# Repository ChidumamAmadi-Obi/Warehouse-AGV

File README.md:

# Warehouse AGV 
*(3rd Year Capstone Project)*

Automated Guided Vehicle that transports loads along predetermined paths. Features line following, obstacle detection, location tracking, and PS4 controller input via Bluetooth. Built with a Finite State Machine (FSM) architecture with LED/buzzer alerts for user feedback.

### Links
 - [**Demo Video**](https://github.com/user-attachments/assets/4ddb8e79-1c91-4d6d-a385-816ef9b9aa53) <br>
 - [*STL Files*](https://github.com/ChidumamAmadi-Obi/Warehouse-AGV/tree/main/mechanical%20design/STL%20FIles) <br>
 - [*Gerber Files*](https://github.com/ChidumamAmadi-Obi/Warehouse-AGV/tree/main/hardware/gerbers-files) <br>
 - [*Schematic Diagram*](https://github.com/ChidumamAmadi-Obi/Warehouse-AGV/blob/main/hardware/schematic-pdf.pdf) <br>
 - [*Firmware Source Code*](https://github.com/ChidumamAmadi-Obi/Warehouse-AGV/tree/main/firmware) <br>

### Features
- PS4 Bluetooth controller for destination waypoints
- Line following with obstacle avoidance
- Real-time location tracking with waypoint markers on track
- Finite State Machine with robust transitions 
- Visual/audio alerts (LEDs & buzzer)
- 3D printable chassis (STL files included)
- Custom PCB with integrated motor driver, voltage regulation and sensor headers

### Firmware Prerequisites
The chosen controller needs to be paired with the ESP32’s Bluetooth MAC address before use.
Additionally, project also relies on [this](https://github.com/pablomarquez76/PS4_Controller_Host/tree/main) ps4 controller library to handle the Bluetooth communication between the ESP32 and the PS4 controller.

Once this library is installed it is to be inserted into the `./lib` PlatformIO project directory

### Custom PCB

### Schematic Diagram

### State Diagram

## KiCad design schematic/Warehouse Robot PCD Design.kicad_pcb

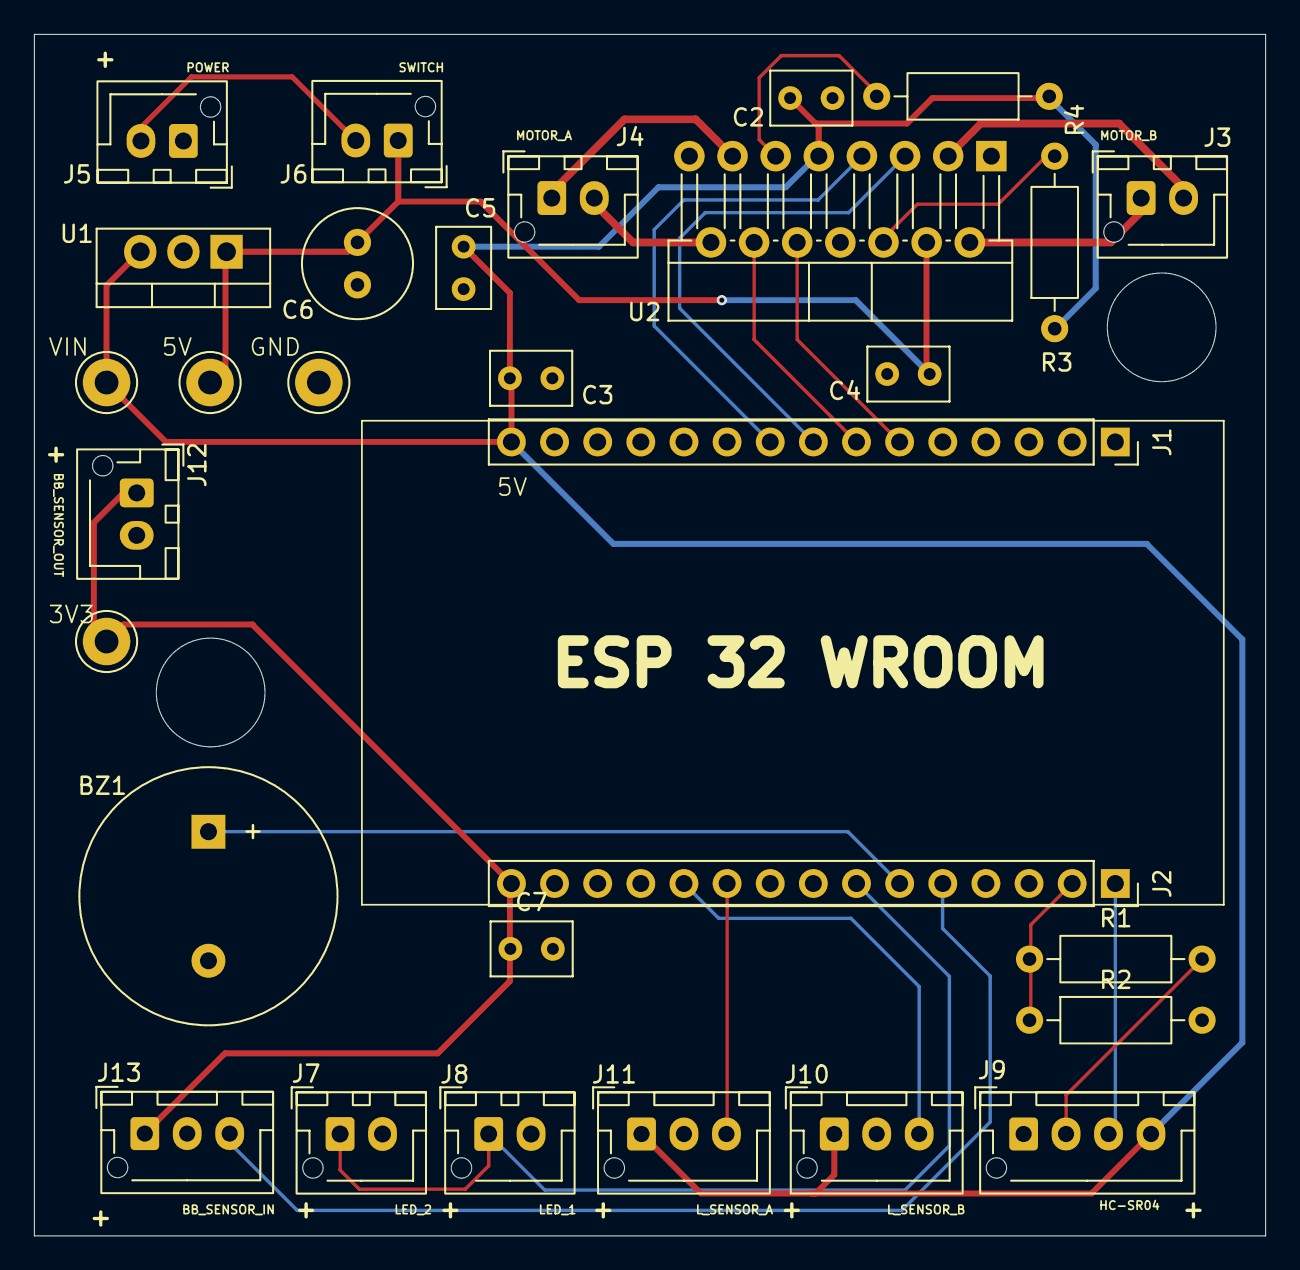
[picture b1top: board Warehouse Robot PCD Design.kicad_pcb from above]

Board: 2 copper layers, 72.5 x 70.8 mm, 30 parts (0 on the bottom side), 23 nets.

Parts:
BZ1: Buzzer; Buzzer_15x7.5RM7.6
C2, C5, C7: 1uf; C_Rect_L4.6mm_W3.0mm_P2.50mm_MKS02_FKP02
C3: 0.1uf; C_Rect_L4.6mm_W3.0mm_P2.50mm_MKS02_FKP02
C4: 10uf; C_Rect_L4.6mm_W3.0mm_P2.50mm_MKS02_FKP02
C6: 10uf; C_Radial_D6.3mm_H5.0mm_P2.50mm
J1, J2: Conn_01x15_Pin; PinSocket_1x15_P2.54mm_Vertical
J3, J4, J5, J6, J7, J8, J12: Conn_01x02; JST_XH_B2B-XH-AM_1x02_P2.50mm_Vertical
J9: Conn_01x04_Pin; JST_XH_B4B-XH-AM_1x04_P2.50mm_Vertical
J10, J11, J13: Conn_01x03_Pin; JST_XH_B3B-XH-AM_1x03_P2.50mm_Vertical
R1, R3, R4: 1k; R_Axial_DIN0207_L6.3mm_D2.5mm_P10.16mm_Horizontal
R2: 2k; R_Axial_DIN0207_L6.3mm_D2.5mm_P10.16mm_Horizontal
TP1, TP2, TP3, TP4: TestPoint; TestPoint_Loop_D3.50mm_Drill1.4mm_Beaded
U1: LM7805_TO220; TO-220-3_Vertical
U2: L298N; TO-220F-15_P2.54x5.08mm_StaggerOdd_Lead5.08mm_Vertical

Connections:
3v3: C7.1, J2.15, J12.1, J13.1, TP1.1
5v: C2.2, C3.1, C5.1, J1.15, J9.4, J10.1, J11.1, R3.1, R4.1, TP2.1, U1.3 (VO), U2.9 (Vss)
BB_OUT: J2.5, J13.3
ECHO: J2.2, R1.2, R2.1
GND: BZ1.2 (-), C2.1, C3.2, C4.1, C5.2, C6.2, C7.2, J1.14, J5.1, J7.2, J8.2, J9.1, J10.2, J11.2, J12.2, J13.2, R2.2, TP4.1, U1.2 (GND), U2.8 (GND)
IN1: J1.8, U2.5 (IN1)
IN2: J1.9, U2.7 (IN2)
IN3: J1.6, U2.10 (IN3)
IN4: J1.7, U2.12 (IN4)
LF_L_OUT: J2.11, J10.3
LF_R_OUT: J2.10, J11.3
unnamed: BZ1.1 (+), J2.6
unnamed: J2.7, J7.1, J8.1
unnamed: J3.1, U2.2 (OUT1)
unnamed: J3.2, U2.3 (OUT2)
unnamed: J4.1, U2.13 (OUT3)
unnamed: J4.2, U2.14 (OUT4)
unnamed: J5.2, J6.2
unnamed: J9.2, R1.1
unnamed: R3.2, U2.6 (EnA)
unnamed: R4.2, U2.11 (EnB)
TRIG: J2.1, J9.3
VIN: C4.2, C6.1, J6.1, TP3.1, U1.1 (VI), U2.4 (Vs)

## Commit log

2025-11-04 Added voltage dividers to sensor outputs
    Voltage dividers were used to convert the output of sensors of a 5V logic level to a 3V3 logic level and safely input into the ESP32
2025-11-07 datasheets for reference
2025-11-12 mechanical design of chassis with solidworks
2025-11-23 added AGV control logic implimentation
    added control logic for the AGV with state based programming and a switch case structure. more comments, explanations and references
2025-11-25 flowchart update
2025-11-26 supports user input destinations
    testing user input destinations, a ps4 controller will be used for this via bluetooth in the future
2025-11-26 updated flowchart
2025-11-27 set up PS4 controller integration
2025-11-29 uploaded state diagram (unfinished)
2025-11-30 updated state diagram
2025-11-30 updated readme with more details
    Added detailed project description and features.
2025-11-30 Add Top Level Design section
    Added Top Level Design section with an image.
2026-01-29 remade/updated schematic in kicad
2026-02-02 updated schematic with test points
2026-02-06 integrated ps4 controller into code, fixed bugs
2026-02-06 Move agv_controller.h to include directory
2026-02-06 merged motor_driver.h and sensor_drivers.h
2026-02-07 PCB design
2026-02-07 Add new PCB design for Warehouse Robot
2026-02-15 updated schematic and pcb design
2026-02-18 Add new PCB preview image to README
2026-04-21 Basic AGV functionality working
    proper package detection
    proper ir line detection
    complete line following algorithm
    complete and fixed state machine
    made function for ir line sensor calibration and AGV line following test
2026-04-27 upload STL files
2026-04-30 Update state diagram image in README
    Replaced the old state diagram image with a new one.
2026-05-01 final firmware changes
    buzzer sounds were made to be less annoying and constant,
    configuration macros fine tuned
2026-05-01 Remove error handling feature from README
    Removed mention of robust error handling and edge cases from features list.
2026-05-01 Add new state diagram image to README
2026-05-19 Rename Warehouse Robot PCB Design.kicad_pcb to PCB-Design.kicad_pcb
2026-05-19 Add Warehouse Robot schematic file
2026-05-19 Rename Warehouse Robot Schematic.pdf to schematic-pdf.pdf
2026-05-20 upload gerber files
2026-05-20 Update README with additional resources and prerequisites
    Added links to demo video, STL files, Gerber files, schematic diagram, and firmware source code. Included firmware prerequisites for PS4 controller integration.
